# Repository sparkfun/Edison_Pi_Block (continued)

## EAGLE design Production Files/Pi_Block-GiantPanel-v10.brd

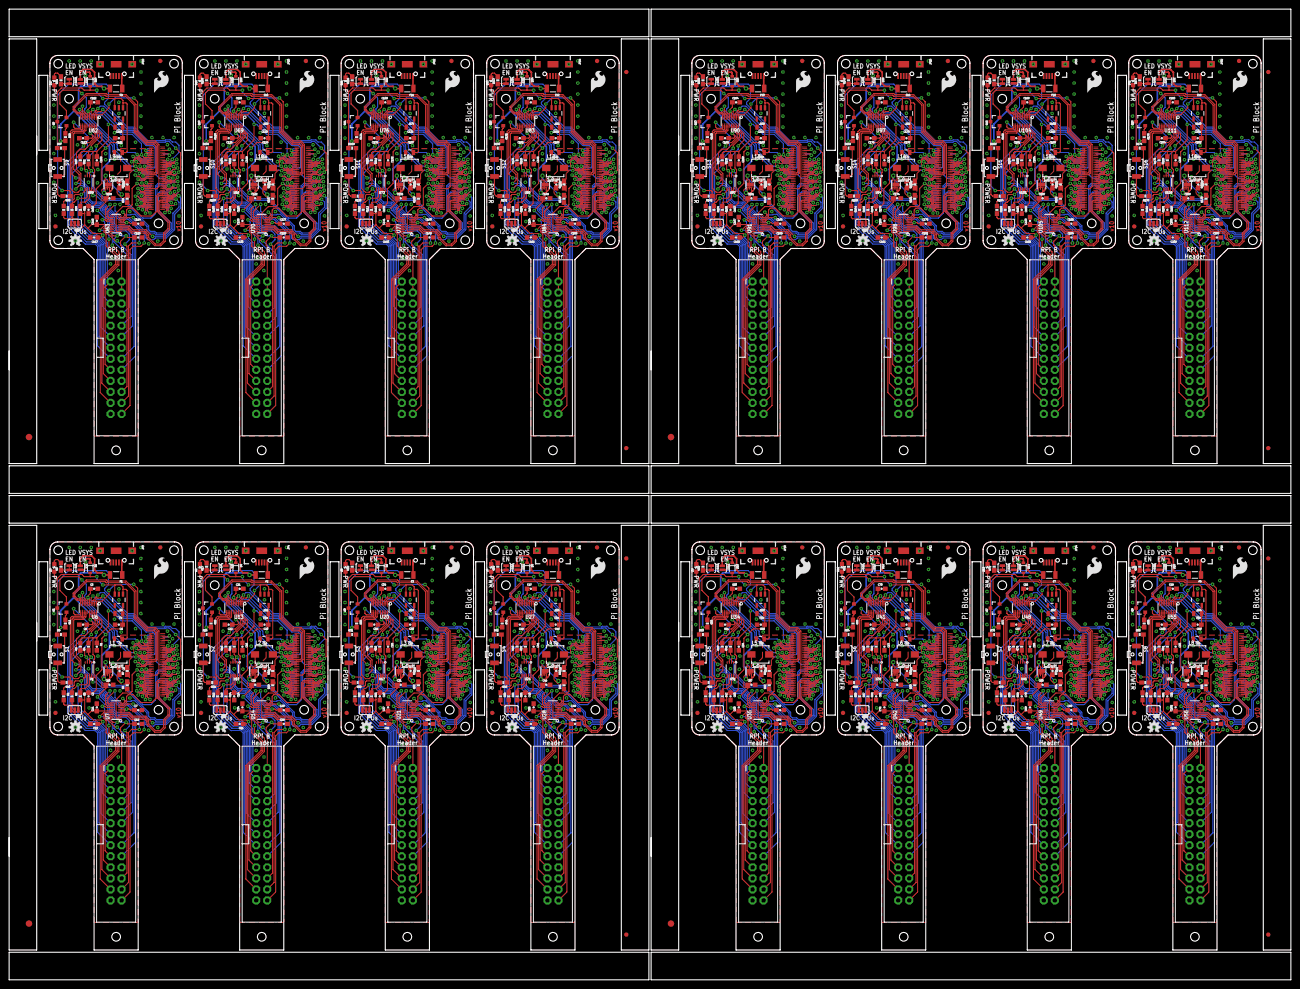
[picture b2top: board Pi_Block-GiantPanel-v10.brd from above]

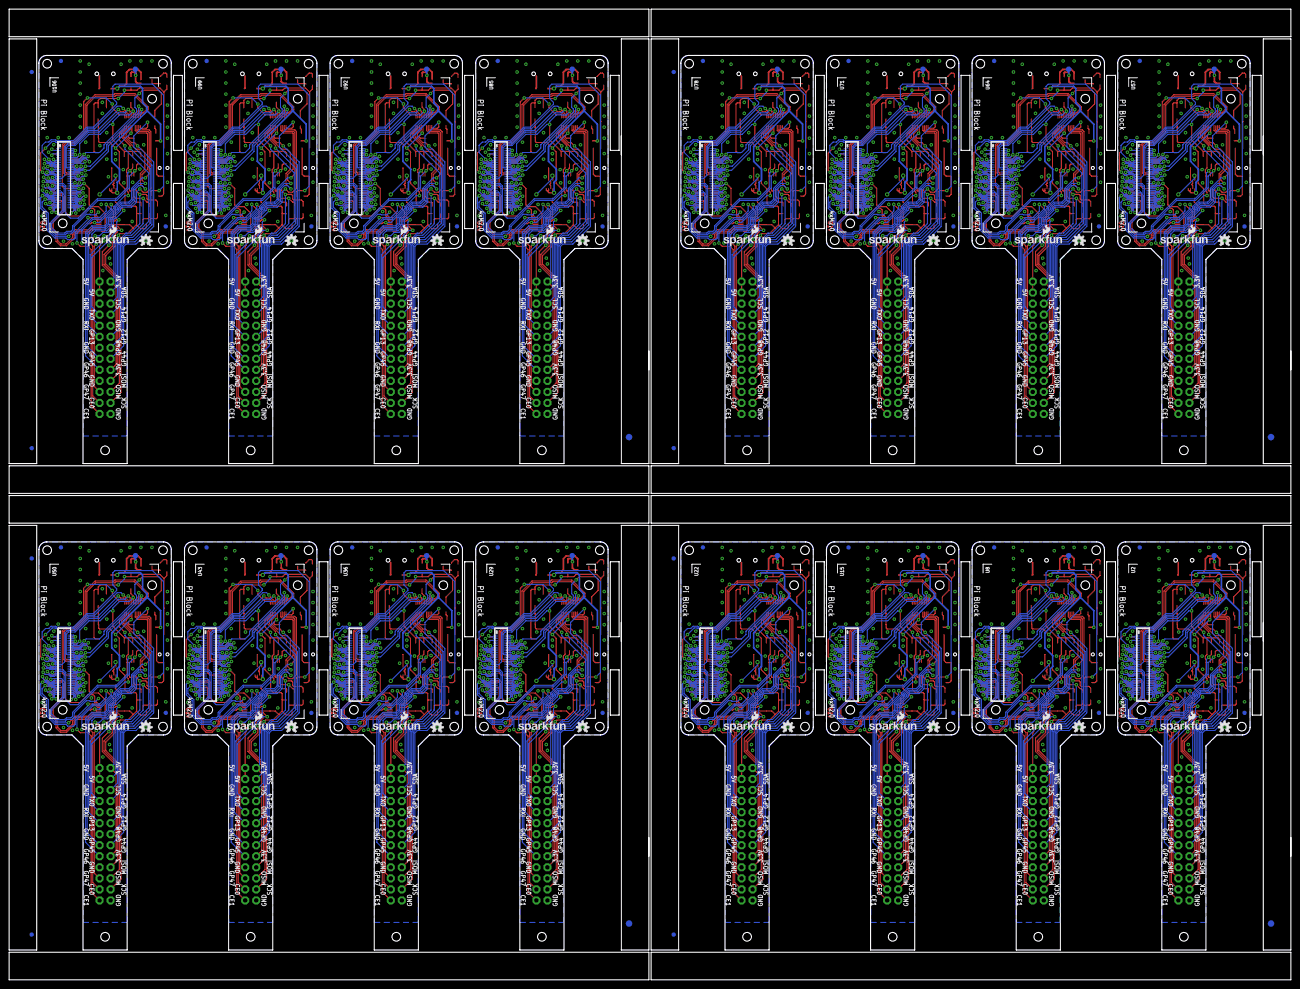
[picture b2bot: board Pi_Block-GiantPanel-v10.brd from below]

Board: 2 copper layers, 295.1 x 223.5 mm, 840 parts (124 on the bottom side), 1408 nets.

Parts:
C1, C2, C4, C5, C6, C7, C11, C14, C15, C20, C21, C22, C23, C24, C27, C28, C33, C34, C35, C36, C37, C40, C41, C46, C47, C48, C49, C50, C53, C54, C59, C60, C61, C62, C63, C66, C67, C72, C73, C74, C75, C76, C79, C80, C85, C86, C87, C88, C89, C92, C93, C98, C99, C100, C101, C102, C105, C106, C111, C112, C113, C114, C115, C118, C119, C124, C125, C126, C127, C128, C131, C132, C137, C138, C139, C140, C141, C144, C145, C150, C151, C152, C153, C154, C157, C158, C163, C164, C165, C166, C167, C170, C171, C176, C177, C178, C179, C180, C183, C184, C189, C190, C191, C192, C193, C196, C197, C202, C203, C204, C205, C206: 0.1uF; 0603-CAP
C3, C19, C32, C45, C58, C71, C84, C97, C110, C123, C136, C149, C162, C175, C188, C201: 10uF; 0805
C8, C16, C29, C42, C55, C68, C81, C94, C107, C120, C133, C146, C159, C172, C185, C198: 22uF; 0805
C9, C17, C30, C43, C56, C69, C82, C95, C108, C121, C134, C147, C160, C173, C186, C199: 9.0pF; 0603-CAP
C10, C18, C31, C44, C57, C70, C83, C96, C109, C122, C135, C148, C161, C174, C187, C200: 4.7uF; 0603-CAP
C12, C13, C25, C26, C38, C39, C51, C52, C64, C65, C77, C78, C90, C91, C103, C104, C116, C117, C129, C130, C142, C143, C155, C156, C168, C169, C181, C182, C194, C195, C207, C208: 1.0uF; 0603-CAP
D1, D4, D6, D8, D10, D12, D14, D16, D18, D20, D22, D24, D26, D28, D30, D32: BAT20J; SOD-323
D2, D3, D5, D7, D9, D11, D13, D15, D17, D19, D21, D23, D25, D27, D29, D31: BLUE; LED-0603
E$1, E$2, E$9, E$10, E$15, E$16, E$21, E$22: FIDUCIAL-1.5X3
E$3, E$4, E$5, E$6, E$7, E$8, E$11, E$12, E$13, E$14, E$17, E$18, E$19, E$20, E$23, E$24: FIDUCIAL-1X2
F1, F2, F3, F4, F5, F6, F7, F8, F9, F10, F11, F12, F13, F14, F15, F16: PTCSMD; PTC-1206
FID1, FID2, FID3, FID4, FID5, FID6, FID7, FID8, FID9, FID10, FID11, FID12, FID13, FID14, FID15, FID16, FID17, FID18, FID19, FID20, FID21, FID22, FID23, FID24, FID25, FID26, FID27, FID28, FID29, FID30, FID31, FID32, FID33, FID34, FID35, FID36, FID37, FID38, FID39, FID40, FID41, FID42, FID43, FID44, FID45, FID46, FID47, FID48, FID49, FID50, FID51, FID52, FID53, FID54, FID55, FID56, FID57, FID58, FID59, FID60, FID61, FID62, FID63, FID64: FIDUCIAL1X2; FIDUCIAL-1X2
JP1, JP2, JP5, JP7, JP9, JP11, JP13, JP15, JP17, JP19, JP21, JP23, JP25, JP27, JP29, JP31: RASPBERRYPI-GPIOPTH; 2X13-SHROUDED
JP3, JP4, JP6, JP8, JP10, JP12, JP14, JP16, JP18, JP20, JP22, JP24, JP26, JP28, JP30, JP32: USB_MICROB; USB-B-MICRO-SMD_V03
L1, L2, L3, L4, L5, L6, L7, L8, L9, L10, L11, L12, L13, L14, L15, L16: 1.0uH; INDUCTOR-SRP4020
LOGO1, LOGO2, LOGO5, LOGO6, LOGO9, LOGO10, LOGO13, LOGO14, LOGO17, LOGO18, LOGO21, LOGO22, LOGO25, LOGO26, LOGO29, LOGO30, LOGO33, LOGO34, LOGO37, LOGO38, LOGO41, LOGO42, LOGO45, LOGO46, LOGO49, LOGO50, LOGO53, LOGO54, LOGO57, LOGO58, LOGO61, LOGO62: OSHW-LOGOS; OSHW-LOGO-S
LOGO3, LOGO8, LOGO12, LOGO16, LOGO20, LOGO24, LOGO28, LOGO32, LOGO36, LOGO40, LOGO44, LOGO48, LOGO52, LOGO56, LOGO60, LOGO64: SFE_LOGO_FLAME.2_INCH; SFE_LOGO_FLAME_.2
LOGO4, LOGO7, LOGO11, LOGO15, LOGO19, LOGO23, LOGO27, LOGO31, LOGO35, LOGO39, LOGO43, LOGO47, LOGO51, LOGO55, LOGO59, LOGO63: SFE_LOGO_NAME_FLAME.1_INCH; SFE_LOGO_NAME_FLAME_.1
Q1, Q2, Q3, Q4, Q5, Q6, Q7, Q8, Q9, Q10, Q11, Q12, Q13, Q14, Q15, Q16: 200mA/50V; SOT23-3
R1, R2, R9, R12, R13, R20, R23, R24, R31, R34, R35, R42, R45, R46, R53, R56, R57, R64, R67, R68, R75, R78, R79, R86, R89, R90, R97, R100, R101, R108, R111, R112, R119, R122, R123, R130, R133, R134, R141, R144, R145, R152, R155, R156, R163, R166, R167, R174: 10K; 0603-RES
R3, R14, R25, R36, R47, R58, R69, R80, R91, R102, R113, R124, R135, R146, R157, R168: 200k; 0603-RES
R4, R5, R15, R16, R26, R27, R37, R38, R48, R49, R59, R60, R70, R71, R81, R82, R92, R93, R103, R104, R114, R115, R125, R126, R136, R137, R147, R148, R158, R159, R169, R170: DNP; 0603-RES
R6, R11, R17, R22, R28, R33, R39, R44, R50, R55, R61, R66, R72, R77, R83, R88, R94, R99, R105, R110, R116, R121, R127, R132, R138, R143, R149, R154, R160, R165, R171, R176: 1K; 0603-RES
R7, R18, R29, R40, R51, R62, R73, R84, R95, R106, R117, R128, R139, R150, R161, R172: 680k; 0603-RES
R8, R19, R30, R41, R52, R63, R74, R85, R96, R107, R118, R129, R140, R151, R162, R173: 120k; 0603-RES
R10, R21, R32, R43, R54, R65, R76, R87, R98, R109, R120, R131, R142, R153, R164, R175: 220; 0603-RES
S1, S2, S3, S4, S5, S6, S7, S8, S9, S10, S11, S12, S13, S14, S15, S16: POWER; TACTILE_SWITCH-SMD-RIGHT-ANGLE
SJ1, SJ5, SJ8, SJ11, SJ14, SJ17, SJ20, SJ23, SJ26, SJ29, SJ32, SJ35, SJ38, SJ41, SJ44, SJ47: JUMPER-PAD-2-NOYES_SILK; PAD-JUMPER-2-NO_YES_SILK
SJ2, SJ6, SJ9, SJ12, SJ15, SJ18, SJ21, SJ24, SJ27, SJ30, SJ33, SJ36, SJ39, SJ42, SJ45, SJ48: JUMPER-PAD-3-NC_BY_PASTE; PAD-JUMPER-3-NC_BY_PASTE_YES_SILK_FULL_BOX
SJ3, SJ4, SJ7, SJ10, SJ13, SJ16, SJ19, SJ22, SJ25, SJ28, SJ31, SJ34, SJ37, SJ40, SJ43, SJ46: JUMPER-PAD-2-NC_BY_TRACE; PAD-JUMPER-2-NC_BY_TRACE_YES_SILK
TP1, TP2, TP3, TP4, TP5, TP6, TP7, TP8, TP9, TP10, TP11, TP12, TP13, TP14, TP15, TP16: TEST-POINT3X5; PAD.03X.05
U1, U10, U17, U24, U31, U38, U45, U52, U59, U66, U73, U80, U87, U94, U101, U108: PCA9306; PCA9306DC-1:1
U2, U8, U15, U22, U29, U36, U43, U50, U57, U64, U71, U78, U85, U92, U99, U106: EDISON_CONNECTOR_FULLMOUNTING_HOLES; EDISON_DAUGHTER
U3, U9, U16, U23, U30, U37, U44, U51, U58, U65, U72, U79, U86, U93, U100, U107: EDISON_CONNECTOR_FULLHEADER; DF40C-70DP-0.4(51)
U4, U11, U18, U25, U32, U39, U46, U53, U60, U67, U74, U81, U88, U95, U102, U109: TPS62065; WSON-8-PAD
U5, U12, U19, U26, U33, U40, U47, U54, U61, U68, U75, U82, U89, U96, U103, U110: MIC5219 3.3V; SOT23-5
U6, U7, U13, U14, U20, U21, U27, U28, U34, U35, U41, U42, U48, U49, U55, U56, U62, U63, U69, U70, U76, U77, U83, U84, U90, U91, U97, U98, U104, U105, U111, U112: TXB0108; UFDFN-20

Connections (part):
1.8V: C1.1, C5.1, C7.1, R4.2, R5.2, U1.1, U2.12, U3.12, U6.5, U6.6, U7.5, U7.6
1.8V1: C15.1, C21.1, C23.1, R15.2, R16.2, U8.12, U9.12, U10.1, U13.5, U13.6, U14.5, U14.6
1.8V2: C28.1, C34.1, C36.1, R26.2, R27.2, U15.12, U16.12, U17.1, U20.5, U20.6, U21.5, U21.6
1.8V3: C41.1, C47.1, C49.1, R37.2, R38.2, U22.12, U23.12, U24.1, U27.5, U27.6, U28.5, U28.6
1.8V4: C54.1, C60.1, C62.1, R48.2, R49.2, U29.12, U30.12, U31.1, U34.5, U34.6, U35.5, U35.6
1.8V5: C67.1, C73.1, C75.1, R59.2, R60.2, U36.12, U37.12, U38.1, U41.5, U41.6, U42.5, U42.6
1.8V6: C80.1, C86.1, C88.1, R70.2, R71.2, U43.12, U44.12, U45.1, U48.5, U48.6, U49.5, U49.6
1.8V7: C93.1, C99.1, C101.1, R81.2, R82.2, U50.12, U51.12, U52.1, U55.5, U55.6, U56.5, U56.6
1.8V8: C106.1, C112.1, C114.1, R92.2, R93.2, U57.12, U58.12, U59.1, U62.5, U62.6, U63.5, U63.6
1.8V9: C119.1, C125.1, C127.1, R103.2, R104.2, U64.12, U65.12, U66.1, U69.5, U69.6, U70.5, U70.6
1.8V10: C132.1, C138.1, C140.1, R114.2, R115.2, U71.12, U72.12, U73.1, U76.5, U76.6, U77.5, U77.6
1.8V11: C145.1, C151.1, C153.1, R125.2, R126.2, U78.12, U79.12, U80.1, U83.5, U83.6, U84.5, U84.6
1.8V12: C158.1, C164.1, C166.1, R136.2, R137.2, U85.12, U86.12, U87.1, U90.5, U90.6, U91.5, U91.6
1.8V13: C171.1, C177.1, C179.1, R147.2, R148.2, U92.12, U93.12, U94.1, U97.5, U97.6, U98.5, U98.6
1.8V14: C184.1, C190.1, C192.1, R158.2, R159.2, U99.12, U100.12, U101.1, U104.5, U104.6, U105.5, U105.6
1.8V15: C197.1, C203.1, C205.1, R169.2, R170.2, U106.12, U107.12, U108.1, U111.5, U111.6, U112.5, U112.6
3.3V: U2.8, U2.10, U3.8, U3.10
3.3V1: U8.8, U8.10, U9.8, U9.10
3.3V2: U15.8, U15.10, U16.8, U16.10
3.3V3: U22.8, U22.10, U23.8, U23.10
3.3V4: U29.8, U29.10, U30.8, U30.10
3.3V5: U36.8, U36.10, U37.8, U37.10
3.3V6: U43.8, U43.10, U44.8, U44.10
3.3V7: U50.8, U50.10, U51.8, U51.10
3.3V8: U57.8, U57.10, U58.8, U58.10
3.3V9: U64.8, U64.10, U65.8, U65.10
3.3V10: U71.8, U71.10, U72.8, U72.10
3.3V11: U78.8, U78.10, U79.8, U79.10
3.3V12: U85.8, U85.10, U86.8, U86.10
3.3V13: U92.8, U92.10, U93.8, U93.10
3.3V14: U99.8, U99.10, U100.8, U100.10
3.3V15: U106.8, U106.10, U107.8, U107.10
3.3V_LOCAL: C2.1, C3.1, C4.1, C6.1, C11.1, C13.1, JP1.1, JP1.17, R3.2, SJ2.2, U5.5, U6.16, U7.16
3.3V_LOCAL1: C14.1, C19.1, C20.1, C22.1, C24.1, C26.1, JP2.1, JP2.17, R14.2, SJ6.2, U12.5, U13.16, U14.16
3.3V_LOCAL2: C27.1, C32.1, C33.1, C35.1, C37.1, C39.1, JP5.1, JP5.17, R25.2, SJ9.2, U19.5, U20.16, U21.16
3.3V_LOCAL3: C40.1, C45.1, C46.1, C48.1, C50.1, C52.1, JP7.1, JP7.17, R36.2, SJ12.2, U26.5, U27.16, U28.16
3.3V_LOCAL4: C53.1, C58.1, C59.1, C61.1, C63.1, C65.1, JP9.1, JP9.17, R47.2, SJ15.2, U33.5, U34.16, U35.16
3.3V_LOCAL5: C66.1, C71.1, C72.1, C74.1, C76.1, C78.1, JP11.1, JP11.17, R58.2, SJ18.2, U40.5, U41.16, U42.16
3.3V_LOCAL6: C79.1, C84.1, C85.1, C87.1, C89.1, C91.1, JP13.1, JP13.17, R69.2, SJ21.2, U47.5, U48.16, U49.16
3.3V_LOCAL7: C92.1, C97.1, C98.1, C100.1, C102.1, C104.1, JP15.1, JP15.17, R80.2, SJ24.2, U54.5, U55.16, U56.16
3.3V_LOCAL8: C105.1, C110.1, C111.1, C113.1, C115.1, C117.1, JP17.1, JP17.17, R91.2, SJ27.2, U61.5, U62.16, U63.16
3.3V_LOCAL9: C118.1, C123.1, C124.1, C126.1, C128.1, C130.1, JP19.1, JP19.17, R102.2, SJ30.2, U68.5, U69.16, U70.16
3.3V_LOCAL10: C131.1, C136.1, C137.1, C139.1, C141.1, C143.1, JP21.1, JP21.17, R113.2, SJ33.2, U75.5, U76.16, U77.16
3.3V_LOCAL11: C144.1, C149.1, C150.1, C152.1, C154.1, C156.1, JP23.1, JP23.17, R124.2, SJ36.2, U82.5, U83.16, U84.16
3.3V_LOCAL12: C157.1, C162.1, C163.1, C165.1, C167.1, C169.1, JP25.1, JP25.17, R135.2, SJ39.2, U89.5, U90.16, U91.16
3.3V_LOCAL13: C170.1, C175.1, C176.1, C178.1, C180.1, C182.1, JP27.1, JP27.17, R146.2, SJ42.2, U96.5, U97.16, U98.16
3.3V_LOCAL14: C183.1, C188.1, C189.1, C191.1, C193.1, C195.1, JP29.1, JP29.17, R157.2, SJ45.2, U103.5, U104.16, U105.16
3.3V_LOCAL15: C196.1, C201.1, C202.1, C204.1, C206.1, C208.1, JP31.1, JP31.17, R168.2, SJ48.2, U110.5, U111.16, U112.16
5V: C10.1, C12.1, F1.2, JP1.2, JP1.4, R11.2, SJ1.1, U4.5, U4.7, U4.8
5V1: C18.1, C25.1, F2.2, JP2.2, JP2.4, R22.2, SJ5.1, U11.5, U11.7, U11.8
5V2: C31.1, C38.1, F3.2, JP5.2, JP5.4, R33.2, SJ8.1, U18.5, U18.7, U18.8
5V3: C44.1, C51.1, F4.2, JP7.2, JP7.4, R44.2, SJ11.1, U25.5, U25.7, U25.8
5V4: C57.1, C64.1, F5.2, JP9.2, JP9.4, R55.2, SJ14.1, U32.5, U32.7, U32.8
5V5: C70.1, C77.1, F6.2, JP11.2, JP11.4, R66.2, SJ17.1, U39.5, U39.7, U39.8
5V6: C83.1, C90.1, F7.2, JP13.2, JP13.4, R77.2, SJ20.1, U46.5, U46.7, U46.8
5V7: C96.1, C103.1, F8.2, JP15.2, JP15.4, R88.2, SJ23.1, U53.5, U53.7, U53.8
5V8: C109.1, C116.1, F9.2, JP17.2, JP17.4, R99.2, SJ26.1, U60.5, U60.7, U60.8
5V9: C122.1, C129.1, F10.2, JP19.2, JP19.4, R110.2, SJ29.1, U67.5, U67.7, U67.8
5V10: C135.1, C142.1, F11.2, JP21.2, JP21.4, R121.2, SJ32.1, U74.5, U74.7, U74.8
5V11: C148.1, C155.1, F12.2, JP23.2, JP23.4, R132.2, SJ35.1, U81.5, U81.7, U81.8
5V12: C161.1, C168.1, F13.2, JP25.2, JP25.4, R143.2, SJ38.1, U88.5, U88.7, U88.8
5V13: C174.1, C181.1, F14.2, JP27.2, JP27.4, R154.2, SJ41.1, U95.5, U95.7, U95.8
5V14: C187.1, C194.1, F15.2, JP29.2, JP29.4, R165.2, SJ44.1, U102.5, U102.7, U102.8
5V15: C200.1, C207.1, F16.2, JP31.2, JP31.4, R176.2, SJ47.1, U109.5, U109.7, U109.8
DCIN: Q1.2, U2.14, U3.14
DCIN1: Q2.2, U8.14, U9.14
DCIN2: Q3.2, U15.14, U16.14
DCIN3: Q4.2, U22.14, U23.14
DCIN4: Q5.2, U29.14, U30.14
DCIN5: Q6.2, U36.14, U37.14
DCIN6: Q7.2, U43.14, U44.14
DCIN7: Q8.2, U50.14, U51.14
DCIN8: Q9.2, U57.14, U58.14
DCIN9: Q10.2, U64.14, U65.14
DCIN10: Q11.2, U71.14, U72.14
DCIN11: Q12.2, U78.14, U79.14
DCIN12: Q13.2, U85.14, U86.14
DCIN13: Q14.2, U92.14, U93.14
DCIN14: Q15.2, U99.14, U100.14
DCIN15: Q16.2, U106.14, U107.14
FAULT: U2.19, U3.19
FAULT1: U8.19, U9.19
FAULT2: U15.19, U16.19
FAULT3: U22.19, U23.19
FAULT4: U29.19, U30.19
FAULT5: U36.19, U37.19
FAULT6: U43.19, U44.19
FAULT7: U50.19, U51.19
FAULT8: U57.19, U58.19
FAULT9: U64.19, U65.19
FAULT10: U71.19, U72.19
FAULT11: U78.19, U79.19
FAULT12: U85.19, U86.19
FAULT13: U92.19, U93.19
FAULT14: U99.19, U100.19
FAULT15: U106.19, U107.19
FW_RCVR: U2.69, U3.69
FW_RCVR1: U8.69, U9.69
FW_RCVR2: U15.69, U16.69
FW_RCVR3: U22.69, U23.69
FW_RCVR4: U29.69, U30.69
FW_RCVR5: U36.69, U37.69
FW_RCVR6: U43.69, U44.69
FW_RCVR7: U50.69, U51.69
FW_RCVR8: U57.69, U58.69
FW_RCVR9: U64.69, U65.69
FW_RCVR10: U71.69, U72.69
FW_RCVR11: U78.69, U79.69
FW_RCVR12: U85.69, U86.69
FW_RCVR13: U92.69, U93.69
FW_RCVR14: U99.69, U100.69
FW_RCVR15: U106.69, U107.69
GND: C1.2, C2.2, C3.2, C4.2, C5.2, C6.2, C7.2, C8.2, C10.2, C11.2, C12.2, C13.2, JP1.6, JP1.9, JP1.14, JP1.20, JP1.25, JP3.GND1, JP3.SHIELD1, JP3.SHIELD2, JP3.SHIELD3, R8.1, S1.1, SJ3.1, U1.4, U2.1, U2.5, U2.9, U2.11, U2.13, U2.15, U3.1, U3.5, U3.9, U3.11, U3.13, U3.15, U4.1, U4.3, U4.6, U4.PAD, U5.2, U6.15, U7.15
GND1: C14.2, C15.2, C16.2, C18.2, C19.2, C20.2, C21.2, C22.2, C23.2, C24.2, C25.2, C26.2, JP2.6, JP2.9, JP2.14, JP2.20, JP2.25, JP4.GND1, JP4.SHIELD1, JP4.SHIELD2, JP4.SHIELD3, R19.1, S2.1, SJ4.1, U8.1, U8.5, U8.9, U8.11, U8.13, U8.15, U9.1, U9.5, U9.9, U9.11, U9.13, U9.15, U10.4, U11.1, U11.3, U11.6, U11.PAD, U12.2, U13.15, U14.15
GND2: C27.2, C28.2, C29.2, C31.2, C32.2, C33.2, C34.2, C35.2, C36.2, C37.2, C38.2, C39.2, JP5.6, JP5.9, JP5.14, JP5.20, JP5.25, JP6.GND1, JP6.SHIELD1, JP6.SHIELD2, JP6.SHIELD3, R30.1, S3.1, SJ7.1, U15.1, U15.5, U15.9, U15.11, U15.13, U15.15, U16.1, U16.5, U16.9, U16.11, U16.13, U16.15, U17.4, U18.1, U18.3, U18.6, U18.PAD, U19.2, U20.15, U21.15
GND3: C40.2, C41.2, C42.2, C44.2, C45.2, C46.2, C47.2, C48.2, C49.2, C50.2, C51.2, C52.2, JP7.6, JP7.9, JP7.14, JP7.20, JP7.25, JP8.GND1, JP8.SHIELD1, JP8.SHIELD2, JP8.SHIELD3, R41.1, S4.1, SJ10.1, U22.1, U22.5, U22.9, U22.11, U22.13, U22.15, U23.1, U23.5, U23.9, U23.11, U23.13, U23.15, U24.4, U25.1, U25.3, U25.6, U25.PAD, U26.2, U27.15, U28.15
GND4: C53.2, C54.2, C55.2, C57.2, C58.2, C59.2, C60.2, C61.2, C62.2, C63.2, C64.2, C65.2, JP9.6, JP9.9, JP9.14, JP9.20, JP9.25, JP10.GND1, JP10.SHIELD1, JP10.SHIELD2, JP10.SHIELD3, R52.1, S5.1, SJ13.1, U29.1, U29.5, U29.9, U29.11, U29.13, U29.15, U30.1, U30.5, U30.9, U30.11, U30.13, U30.15, U31.4, U32.1, U32.3, U32.6, U32.PAD, U33.2, U34.15, U35.15
GND5: C66.2, C67.2, C68.2, C70.2, C71.2, C72.2, C73.2, C74.2, C75.2, C76.2, C77.2, C78.2, JP11.6, JP11.9, JP11.14, JP11.20, JP11.25, JP12.GND1, JP12.SHIELD1, JP12.SHIELD2, JP12.SHIELD3, R63.1, S6.1, SJ16.1, U36.1, U36.5, U36.9, U36.11, U36.13, U36.15, U37.1, U37.5, U37.9, U37.11, U37.13, U37.15, U38.4, U39.1, U39.3, U39.6, U39.PAD, U40.2, U41.15, U42.15
GND6: C79.2, C80.2, C81.2, C83.2, C84.2, C85.2, C86.2, C87.2, C88.2, C89.2, C90.2, C91.2, JP13.6, JP13.9, JP13.14, JP13.20, JP13.25, JP14.GND1, JP14.SHIELD1, JP14.SHIELD2, JP14.SHIELD3, R74.1, S7.1, SJ19.1, U43.1, U43.5, U43.9, U43.11, U43.13, U43.15, U44.1, U44.5, U44.9, U44.11, U44.13, U44.15, U45.4, U46.1, U46.3, U46.6, U46.PAD, U47.2, U48.15, U49.15
GND7: C92.2, C93.2, C94.2, C96.2, C97.2, C98.2, C99.2, C100.2, C101.2, C102.2, C103.2, C104.2, JP15.6, JP15.9, JP15.14, JP15.20, JP15.25, JP16.GND1, JP16.SHIELD1, JP16.SHIELD2, JP16.SHIELD3, R85.1, S8.1, SJ22.1, U50.1, U50.5, U50.9, U50.11, U50.13, U50.15, U51.1, U51.5, U51.9, U51.11, U51.13, U51.15, U52.4, U53.1, U53.3, U53.6, U53.PAD, U54.2, U55.15, U56.15
GND8: C105.2, C106.2, C107.2, C109.2, C110.2, C111.2, C112.2, C113.2, C114.2, C115.2, C116.2, C117.2, JP17.6, JP17.9, JP17.14, JP17.20, JP17.25, JP18.GND1, JP18.SHIELD1, JP18.SHIELD2, JP18.SHIELD3, R96.1, S9.1, SJ25.1, U57.1, U57.5, U57.9, U57.11, U57.13, U57.15, U58.1, U58.5, U58.9, U58.11, U58.13, U58.15, U59.4, U60.1, U60.3, U60.6, U60.PAD, U61.2, U62.15, U63.15
GND9: C118.2, C119.2, C120.2, C122.2, C123.2, C124.2, C125.2, C126.2, C127.2, C128.2, C129.2, C130.2, JP19.6, JP19.9, JP19.14, JP19.20, JP19.25, JP20.GND1, JP20.SHIELD1, JP20.SHIELD2, JP20.SHIELD3, R107.1, S10.1, SJ28.1, U64.1, U64.5, U64.9, U64.11, U64.13, U64.15, U65.1, U65.5, U65.9, U65.11, U65.13, U65.15, U66.4, U67.1, U67.3, U67.6, U67.PAD, U68.2, U69.15, U70.15
GND10: C131.2, C132.2, C133.2, C135.2, C136.2, C137.2, C138.2, C139.2, C140.2, C141.2, C142.2, C143.2, JP21.6, JP21.9, JP21.14, JP21.20, JP21.25, JP22.GND1, JP22.SHIELD1, JP22.SHIELD2, JP22.SHIELD3, R118.1, S11.1, SJ31.1, U71.1, U71.5, U71.9, U71.11, U71.13, U71.15, U72.1, U72.5, U72.9, U72.11, U72.13, U72.15, U73.4, U74.1, U74.3, U74.6, U74.PAD, U75.2, U76.15, U77.15
GND11: C144.2, C145.2, C146.2, C148.2, C149.2, C150.2, C151.2, C152.2, C153.2, C154.2, C155.2, C156.2, JP23.6, JP23.9, JP23.14, JP23.20, JP23.25, JP24.GND1, JP24.SHIELD1, JP24.SHIELD2, JP24.SHIELD3, R129.1, S12.1, SJ34.1, U78.1, U78.5, U78.9, U78.11, U78.13, U78.15, U79.1, U79.5, U79.9, U79.11, U79.13, U79.15, U80.4, U81.1, U81.3, U81.6, U81.PAD, U82.2, U83.15, U84.15
GND12: C157.2, C158.2, C159.2, C161.2, C162.2, C163.2, C164.2, C165.2, C166.2, C167.2, C168.2, C169.2, JP25.6, JP25.9, JP25.14, JP25.20, JP25.25, JP26.GND1, JP26.SHIELD1, JP26.SHIELD2, JP26.SHIELD3, R140.1, S13.1, SJ37.1, U85.1, U85.5, U85.9, U85.11, U85.13, U85.15, U86.1, U86.5, U86.9, U86.11, U86.13, U86.15, U87.4, U88.1, U88.3, U88.6, U88.PAD, U89.2, U90.15, U91.15
GND13: C170.2, C171.2, C172.2, C174.2, C175.2, C176.2, C177.2, C178.2, C179.2, C180.2, C181.2, C182.2, JP27.6, JP27.9, JP27.14, JP27.20, JP27.25, JP28.GND1, JP28.SHIELD1, JP28.SHIELD2, JP28.SHIELD3, R151.1, S14.1, SJ40.1, U92.1, U92.5, U92.9, U92.11, U92.13, U92.15, U93.1, U93.5, U93.9, U93.11, U93.13, U93.15, U94.4, U95.1, U95.3, U95.6, U95.PAD, U96.2, U97.15, U98.15
GND14: C183.2, C184.2, C185.2, C187.2, C188.2, C189.2, C190.2, C191.2, C192.2, C193.2, C194.2, C195.2, JP29.6, JP29.9, JP29.14, JP29.20, JP29.25, JP30.GND1, JP30.SHIELD1, JP30.SHIELD2, JP30.SHIELD3, R162.1, S15.1, SJ43.1, U99.1, U99.5, U99.9, U99.11, U99.13, U99.15, U100.1, U100.5, U100.9, U100.11, U100.13, U100.15, U101.4, U102.1, U102.3, U102.6, U102.PAD, U103.2, U104.15, U105.15
GND15: C196.2, C197.2, C198.2, C200.2, C201.2, C202.2, C203.2, C204.2, C205.2, C206.2, C207.2, C208.2, JP31.6, JP31.9, JP31.14, JP31.20, JP31.25, JP32.GND1, JP32.SHIELD1, JP32.SHIELD2, JP32.SHIELD3, R173.1, S16.1, SJ46.1, U106.1, U106.5, U106.9, U106.11, U106.13, U106.15, U107.1, U107.5, U107.9, U107.11, U107.13, U107.15, U108.4, U109.1, U109.3, U109.6, U109.PAD, U110.2, U111.15, U112.15
GP1: U8.48, U9.48, U13.1
GP2: U8.42, U9.42
GP3: U8.34, U9.34
GP4: U8.32, U9.32, U13.10
GP5: U8.30, U9.30, U13.9
GP6: U8.28, U9.28, U13.8
GP7: U8.26, U9.26, U13.7
GP8: U8.25, U9.25
GP9: U8.24, U9.24, U13.4
GP10: U15.48, U16.48, U20.1
GP11: U15.42, U16.42
GP12: U15.34, U16.34
GP12_PWM0: U2.35, U3.35, U6.2
GP12_PWM1: U8.35, U9.35, U13.2
GP12_PWM2: U15.35, U16.35, U20.2
GP12_PWM3: U22.35, U23.35, U27.2
GP12_PWM4: U29.35, U30.35, U34.2
GP12_PWM5: U36.35, U37.35, U41.2
GP12_PWM6: U43.35, U44.35, U48.2
GP12_PWM7: U50.35, U51.35, U55.2
GP12_PWM8: U57.35, U58.35, U62.2
GP12_PWM9: U64.35, U65.35, U69.2
GP12_PWM10: U71.35, U72.35, U76.2
GP12_PWM11: U78.35, U79.35, U83.2
GP12_PWM12: U85.35, U86.35, U90.2
GP12_PWM13: U92.35, U93.35, U97.2
GP12_PWM14: U99.35, U100.35, U104.2
GP12_PWM15: U106.35, U107.35, U111.2
GP13: U15.32, U16.32, U20.10
GP13_PWM1: U2.33, U3.33, U6.3
GP13_PWM2: U8.33, U9.33, U13.3
GP13_PWM3: U15.33, U16.33, U20.3
GP13_PWM4: U22.33, U23.33, U27.3
GP13_PWM5: U29.33, U30.33, U34.3
GP13_PWM6: U36.33, U37.33, U41.3
GP13_PWM7: U43.33, U44.33, U48.3
GP13_PWM8: U50.33, U51.33, U55.3
GP13_PWM9: U57.33, U58.33, U62.3
GP13_PWM10: U64.33, U65.33, U69.3
GP13_PWM11: U71.33, U72.33, U76.3
GP13_PWM12: U78.33, U79.33, U83.3
GP13_PWM13: U85.33, U86.33, U90.3
GP13_PWM14: U92.33, U93.33, U97.3
GP13_PWM15: U99.33, U100.33, U104.3
GP13_PWM16: U106.33, U107.33, U111.3
GP14: U2.48, U3.48, U6.1
GP15: U2.42, U3.42
GP16: U15.30, U16.30, U20.9
GP17: U15.28, U16.28, U20.8
GP18: U15.26, U16.26, U20.7
GP19: U15.25, U16.25
GP19_I2C_1_SCL: R4.1, U1.2, U2.41, U3.41
GP19_I2C_1_SCL1: R15.1, U8.41, U9.41, U10.2
GP19_I2C_1_SCL2: R26.1, U15.41, U16.41, U17.2
GP19_I2C_1_SCL3: R37.1, U22.41, U23.41, U24.2
GP19_I2C_1_SCL4: R48.1, U29.41, U30.41, U31.2
GP19_I2C_1_SCL5: R59.1, U36.41, U37.41, U38.2
GP19_I2C_1_SCL6: R70.1, U43.41, U44.41, U45.2
GP19_I2C_1_SCL7: R81.1, U50.41, U51.41, U52.2
GP19_I2C_1_SCL8: R92.1, U57.41, U58.41, U59.2
GP19_I2C_1_SCL9: R103.1, U64.41, U65.41, U66.2
GP19_I2C_1_SCL10: R114.1, U71.41, U72.41, U73.2
GP19_I2C_1_SCL11: R125.1, U78.41, U79.41, U80.2
GP19_I2C_1_SCL12: R136.1, U85.41, U86.41, U87.2
GP19_I2C_1_SCL13: R147.1, U92.41, U93.41, U94.2
GP19_I2C_1_SCL14: R158.1, U99.41, U100.41, U101.2
GP19_I2C_1_SCL15: R169.1, U106.41, U107.41, U108.2
GP20: U15.24, U16.24, U20.4
GP20_I2C_1_SDA: R5.1, U1.3, U2.43, U3.43
GP20_I2C_1_SDA1: R16.1, U8.43, U9.43, U10.3
GP20_I2C_1_SDA2: R27.1, U15.43, U16.43, U17.3
GP20_I2C_1_SDA3: R38.1, U22.43, U23.43, U24.3
GP20_I2C_1_SDA4: R49.1, U29.43, U30.43, U31.3
GP20_I2C_1_SDA5: R60.1, U36.43, U37.43, U38.3
GP20_I2C_1_SDA6: R71.1, U43.43, U44.43, U45.3
GP20_I2C_1_SDA7: R82.1, U50.43, U51.43, U52.3
GP20_I2C_1_SDA8: R93.1, U57.43, U58.43, U59.3
GP20_I2C_1_SDA9: R104.1, U64.43, U65.43, U66.3
GP20_I2C_1_SDA10: R115.1, U71.43, U72.43, U73.3
GP20_I2C_1_SDA11: R126.1, U78.43, U79.43, U80.3
GP20_I2C_1_SDA12: R137.1, U85.43, U86.43, U87.3
GP20_I2C_1_SDA13: R148.1, U92.43, U93.43, U94.3
GP20_I2C_1_SDA14: R159.1, U99.43, U100.43, U101.3
GP20_I2C_1_SDA15: R170.1, U106.43, U107.43, U108.3
GP21: U22.48, U23.48, U27.1
GP22: U22.42, U23.42
GP23: U22.34, U23.34
GP24: U22.32, U23.32, U27.10
GP25: U22.30, U23.30, U27.9
GP26: U22.28, U23.28, U27.8
GP27: U22.26, U23.26, U27.7
GP27_I2C_6_SCL: U2.45, U3.45
GP27_I2C_6_SCL1: U8.45, U9.45
GP27_I2C_6_SCL2: U15.45, U16.45
GP27_I2C_6_SCL3: U22.45, U23.45
GP27_I2C_6_SCL4: U29.45, U30.45
GP27_I2C_6_SCL5: U36.45, U37.45
GP27_I2C_6_SCL6: U43.45, U44.45
GP27_I2C_6_SCL7: U50.45, U51.45
GP27_I2C_6_SCL8: U57.45, U58.45
GP27_I2C_6_SCL9: U64.45, U65.45
GP27_I2C_6_SCL10: U71.45, U72.45
GP27_I2C_6_SCL11: U78.45, U79.45
GP27_I2C_6_SCL12: U85.45, U86.45
GP27_I2C_6_SCL13: U92.45, U93.45
GP27_I2C_6_SCL14: U99.45, U100.45
GP27_I2C_6_SCL15: U106.45, U107.45
GP28: U22.25, U23.25
GP28_I2C_6_SDA: U2.47, U3.47
GP28_I2C_6_SDA1: U8.47, U9.47
GP28_I2C_6_SDA2: U15.47, U16.47
GP28_I2C_6_SDA3: U22.47, U23.47
GP28_I2C_6_SDA4: U29.47, U30.47
GP28_I2C_6_SDA5: U36.47, U37.47
GP28_I2C_6_SDA6: U43.47, U44.47
GP28_I2C_6_SDA7: U50.47, U51.47
GP28_I2C_6_SDA8: U57.47, U58.47
GP28_I2C_6_SDA9: U64.47, U65.47
GP28_I2C_6_SDA10: U71.47, U72.47
GP28_I2C_6_SDA11: U78.47, U79.47
GP28_I2C_6_SDA12: U85.47, U86.47
GP28_I2C_6_SDA13: U92.47, U93.47
GP28_I2C_6_SDA14: U99.47, U100.47
GP28_I2C_6_SDA15: U106.47, U107.47
GP29: U22.24, U23.24, U27.4
GP30: U29.48, U30.48, U34.1
GP31: U29.42, U30.42
GP32: U29.34, U30.34
GP33: U29.32, U30.32, U34.10
GP34: U29.30, U30.30, U34.9
GP35: U29.28, U30.28, U34.8
GP36: U29.26, U30.26, U34.7
GP37: U29.25, U30.25
GP38: U29.24, U30.24, U34.4
GP39: U36.48, U37.48, U41.1
GP40: U36.42, U37.42
GP40_I2S_2_CLK: U2.52, U3.52
GP40_I2S_2_CLK1: U8.52, U9.52
GP40_I2S_2_CLK2: U15.52, U16.52
GP40_I2S_2_CLK3: U22.52, U23.52
GP40_I2S_2_CLK4: U29.52, U30.52
GP40_I2S_2_CLK5: U36.52, U37.52
GP40_I2S_2_CLK6: U43.52, U44.52
GP40_I2S_2_CLK7: U50.52, U51.52
GP40_I2S_2_CLK8: U57.52, U58.52
GP40_I2S_2_CLK9: U64.52, U65.52
GP40_I2S_2_CLK10: U71.52, U72.52
GP40_I2S_2_CLK11: U78.52, U79.52
GP40_I2S_2_CLK12: U85.52, U86.52
GP40_I2S_2_CLK13: U92.52, U93.52
GP40_I2S_2_CLK14: U99.52, U100.52
GP40_I2S_2_CLK15: U106.52, U107.52
GP41: U36.34, U37.34
GP41_I2S_2_FS: U2.54, U3.54
GP41_I2S_2_FS1: U8.54, U9.54
GP41_I2S_2_FS2: U15.54, U16.54
GP41_I2S_2_FS3: U22.54, U23.54
GP41_I2S_2_FS4: U29.54, U30.54
GP41_I2S_2_FS5: U36.54, U37.54
GP41_I2S_2_FS6: U43.54, U44.54
GP41_I2S_2_FS7: U50.54, U51.54
GP41_I2S_2_FS8: U57.54, U58.54
GP41_I2S_2_FS9: U64.54, U65.54
GP41_I2S_2_FS10: U71.54, U72.54
GP41_I2S_2_FS11: U78.54, U79.54
GP41_I2S_2_FS12: U85.54, U86.54
GP41_I2S_2_FS13: U92.54, U93.54
GP41_I2S_2_FS14: U99.54, U100.54
GP41_I2S_2_FS15: U106.54, U107.54
GP42: U36.32, U37.32, U41.10
GP42_I2S_2_RXD: U2.50, U3.50
GP42_I2S_2_RXD1: U8.50, U9.50
GP42_I2S_2_RXD2: U15.50, U16.50
GP42_I2S_2_RXD3: U22.50, U23.50
GP42_I2S_2_RXD4: U29.50, U30.50
GP42_I2S_2_RXD5: U36.50, U37.50
GP42_I2S_2_RXD6: U43.50, U44.50
GP42_I2S_2_RXD7: U50.50, U51.50
GP42_I2S_2_RXD8: U57.50, U58.50
GP42_I2S_2_RXD9: U64.50, U65.50
GP42_I2S_2_RXD10: U71.50, U72.50
GP42_I2S_2_RXD11: U78.50, U79.50
GP42_I2S_2_RXD12: U85.50, U86.50
GP42_I2S_2_RXD13: U92.50, U93.50
GP42_I2S_2_RXD14: U99.50, U100.50
GP42_I2S_2_RXD15: U106.50, U107.50
GP43: U36.30, U37.30, U41.9
GP43_I2S_2_TXD: U2.56, U3.56
GP43_I2S_2_TXD1: U8.56, U9.56
GP43_I2S_2_TXD2: U15.56, U16.56
GP43_I2S_2_TXD3: U22.56, U23.56
GP43_I2S_2_TXD4: U29.56, U30.56
GP43_I2S_2_TXD5: U36.56, U37.56
GP43_I2S_2_TXD6: U43.56, U44.56
GP43_I2S_2_TXD7: U50.56, U51.56
GP43_I2S_2_TXD8: U57.56, U58.56
GP43_I2S_2_TXD9: U64.56, U65.56
GP43_I2S_2_TXD10: U71.56, U72.56
GP43_I2S_2_TXD11: U78.56, U79.56
GP43_I2S_2_TXD12: U85.56, U86.56
GP43_I2S_2_TXD13: U92.56, U93.56
GP43_I2S_2_TXD14: U99.56, U100.56
GP43_I2S_2_TXD15: U106.56, U107.56
GP44: U2.24, U3.24, U6.4
GP45: U2.26, U3.26, U6.7
GP46: U2.28, U3.28, U6.8
GP47: U2.30, U3.30, U6.9
GP48: U2.32, U3.32, U6.10
GP49: U2.34, U3.34
GP50: U36.28, U37.28, U41.8
GP51: U36.26, U37.26, U41.7
GP52: U36.25, U37.25
GP53: U36.24, U37.24, U41.4
GP54: U43.48, U44.48, U48.1
GP55: U43.42, U44.42
GP56: U43.34, U44.34
GP57: U43.32, U44.32, U48.10
GP58: U43.30, U44.30, U48.9
GP59: U43.28, U44.28, U48.8
GP60: U43.26, U44.26, U48.7
GP61: U43.25, U44.25
GP62: U43.24, U44.24, U48.4
GP63: U50.48, U51.48, U55.1
GP64: U50.42, U51.42
GP65: U50.34, U51.34
GP66: U50.32, U51.32, U55.10
GP67: U50.30, U51.30, U55.9
GP68: U50.28, U51.28, U55.8
GP69: U50.26, U51.26, U55.7
GP70: U50.25, U51.25
GP71: U50.24, U51.24, U55.4
GP72: U57.48, U58.48, U62.1
GP73: U57.42, U58.42
GP74: U57.34, U58.34
GP75: U57.32, U58.32, U62.10
GP76: U57.30, U58.30, U62.9
GP77: U57.28, U58.28, U62.8
GP77_SD_0_CD#: U2.60, U3.60
GP77_SD_0_CD#1: U8.60, U9.60
GP77_SD_0_CD#2: U15.60, U16.60
GP77_SD_0_CD#3: U22.60, U23.60
GP77_SD_0_CD#4: U29.60, U30.60
GP77_SD_0_CD#5: U36.60, U37.60
GP77_SD_0_CD#6: U43.60, U44.60
GP77_SD_0_CD#7: U50.60, U51.60
GP77_SD_0_CD#8: U57.60, U58.60
GP77_SD_0_CD#9: U64.60, U65.60
GP77_SD_0_CD#10: U71.60, U72.60
GP77_SD_0_CD#11: U78.60, U79.60
GP77_SD_0_CD#12: U85.60, U86.60
GP77_SD_0_CD#13: U92.60, U93.60
GP77_SD_0_CD#14: U99.60, U100.60
GP77_SD_0_CD#15: U106.60, U107.60
GP78: U57.26, U58.26, U62.7
GP78_SD_0_CLK: U2.58, U3.58
GP78_SD_0_CLK1: U8.58, U9.58
GP78_SD_0_CLK2: U15.58, U16.58
GP78_SD_0_CLK3: U22.58, U23.58
GP78_SD_0_CLK4: U29.58, U30.58
GP78_SD_0_CLK5: U36.58, U37.58
GP78_SD_0_CLK6: U43.58, U44.58
GP78_SD_0_CLK7: U50.58, U51.58
GP78_SD_0_CLK8: U57.58, U58.58
GP78_SD_0_CLK9: U64.58, U65.58
GP78_SD_0_CLK10: U71.58, U72.58
GP78_SD_0_CLK11: U78.58, U79.58
GP78_SD_0_CLK12: U85.58, U86.58
GP78_SD_0_CLK13: U92.58, U93.58
GP78_SD_0_CLK14: U99.58, U100.58
GP78_SD_0_CLK15: U106.58, U107.58
GP79: U57.25, U58.25
GP79_SD_0_CMD: U2.62, U3.62
GP79_SD_0_CMD1: U8.62, U9.62
GP79_SD_0_CMD2: U15.62, U16.62
GP79_SD_0_CMD3: U22.62, U23.62
GP79_SD_0_CMD4: U29.62, U30.62
GP79_SD_0_CMD5: U36.62, U37.62
GP79_SD_0_CMD6: U43.62, U44.62
GP79_SD_0_CMD7: U50.62, U51.62
GP79_SD_0_CMD8: U57.62, U58.62
GP79_SD_0_CMD9: U64.62, U65.62
GP79_SD_0_CMD10: U71.62, U72.62
GP79_SD_0_CMD11: U78.62, U79.62
GP79_SD_0_CMD12: U85.62, U86.62
GP79_SD_0_CMD13: U92.62, U93.62
GP79_SD_0_CMD14: U99.62, U100.62
GP79_SD_0_CMD15: U106.62, U107.62
GP80: U57.24, U58.24, U62.4
GP80_SD_0_DAT0: U2.66, U3.66
GP80_SD_0_DAT1: U8.66, U9.66
GP80_SD_0_DAT2: U15.66, U16.66
GP80_SD_0_DAT3: U22.66, U23.66
GP80_SD_0_DAT4: U29.66, U30.66
GP80_SD_0_DAT5: U36.66, U37.66
GP80_SD_0_DAT6: U43.66, U44.66
GP80_SD_0_DAT7: U50.66, U51.66
GP80_SD_0_DAT8: U57.66, U58.66
GP80_SD_0_DAT9: U64.66, U65.66
GP80_SD_0_DAT10: U71.66, U72.66
GP80_SD_0_DAT11: U78.66, U79.66
GP80_SD_0_DAT12: U85.66, U86.66
GP80_SD_0_DAT13: U92.66, U93.66
GP80_SD_0_DAT14: U99.66, U100.66
GP80_SD_0_DAT15: U106.66, U107.66
GP81: U64.48, U65.48, U69.1
GP81_SD_0_DAT1: U2.70, U3.70
GP81_SD_0_DAT2: U8.70, U9.70
GP81_SD_0_DAT3: U15.70, U16.70
GP81_SD_0_DAT4: U22.70, U23.70
GP81_SD_0_DAT5: U29.70, U30.70
GP81_SD_0_DAT6: U36.70, U37.70
GP81_SD_0_DAT7: U43.70, U44.70
GP81_SD_0_DAT8: U50.70, U51.70
GP81_SD_0_DAT9: U57.70, U58.70
GP81_SD_0_DAT10: U64.70, U65.70
GP81_SD_0_DAT11: U71.70, U72.70
GP81_SD_0_DAT12: U78.70, U79.70
GP81_SD_0_DAT13: U85.70, U86.70
GP81_SD_0_DAT14: U92.70, U93.70
GP81_SD_0_DAT15: U99.70, U100.70
GP81_SD_0_DAT16: U106.70, U107.70
GP82: U64.42, U65.42
GP82_SD_0_DAT1: U8.64, U9.64
GP82_SD_0_DAT2: U2.64, U3.64
GP82_SD_0_DAT3: U15.64, U16.64
GP82_SD_0_DAT4: U22.64, U23.64
GP82_SD_0_DAT5: U29.64, U30.64
GP82_SD_0_DAT6: U36.64, U37.64
GP82_SD_0_DAT7: U43.64, U44.64
GP82_SD_0_DAT8: U50.64, U51.64
GP82_SD_0_DAT9: U57.64, U58.64
GP82_SD_0_DAT10: U64.64, U65.64
GP82_SD_0_DAT11: U71.64, U72.64
GP82_SD_0_DAT12: U78.64, U79.64
GP82_SD_0_DAT13: U85.64, U86.64
GP82_SD_0_DAT14: U92.64, U93.64
GP82_SD_0_DAT15: U99.64, U100.64
GP82_SD_0_DAT16: U106.64, U107.64
GP83: U64.34, U65.34
GP83_SD_0_DAT1: U8.68, U9.68
GP83_SD_0_DAT2: U15.68, U16.68
GP83_SD_0_DAT3: U2.68, U3.68
GP83_SD_0_DAT4: U22.68, U23.68
GP83_SD_0_DAT5: U29.68, U30.68
GP83_SD_0_DAT6: U36.68, U37.68
GP83_SD_0_DAT7: U43.68, U44.68
GP83_SD_0_DAT8: U50.68, U51.68
GP83_SD_0_DAT9: U57.68, U58.68
GP83_SD_0_DAT10: U64.68, U65.68
GP83_SD_0_DAT11: U71.68, U72.68
GP83_SD_0_DAT12: U78.68, U79.68
GP83_SD_0_DAT13: U85.68, U86.68
GP83_SD_0_DAT14: U92.68, U93.68
GP83_SD_0_DAT15: U99.68, U100.68
GP83_SD_0_DAT16: U106.68, U107.68
GP84: U64.32, U65.32, U69.10
GP84_SD_CLK_FB: U2.44, U3.44
GP84_SD_CLK_FB1: U8.44, U9.44
GP84_SD_CLK_FB2: U15.44, U16.44
GP84_SD_CLK_FB3: U22.44, U23.44
GP84_SD_CLK_FB4: U29.44, U30.44
GP84_SD_CLK_FB5: U36.44, U37.44
GP84_SD_CLK_FB6: U43.44, U44.44
GP84_SD_CLK_FB7: U50.44, U51.44
GP84_SD_CLK_FB8: U57.44, U58.44
GP84_SD_CLK_FB9: U64.44, U65.44
GP84_SD_CLK_FB10: U71.44, U72.44
GP84_SD_CLK_FB11: U78.44, U79.44
GP84_SD_CLK_FB12: U85.44, U86.44
GP84_SD_CLK_FB13: U92.44, U93.44
GP84_SD_CLK_FB14: U99.44, U100.44
GP84_SD_CLK_FB15: U106.44, U107.44
GP85: U64.30, U65.30, U69.9
GP86: U64.28, U65.28, U69.8
GP87: U64.26, U65.26, U69.7
GP88: U64.25, U65.25
GP89: U64.24, U65.24, U69.4
GP90: U71.48, U72.48, U76.1
GP91: U71.42, U72.42
GP92: U71.34, U72.34
GP93: U71.32, U72.32, U76.10
GP94: U71.30, U72.30, U76.9
GP95: U71.28, U72.28, U76.8
GP96: U71.26, U72.26, U76.7
GP97: U71.25, U72.25
GP98: U71.24, U72.24, U76.4
GP99: U78.48, U79.48, U83.1
GP100: U78.42, U79.42
GP101: U78.34, U79.34
GP102: U78.32, U79.32, U83.10
GP103: U78.30, U79.30, U83.9
GP104: U78.28, U79.28, U83.8
GP105: U78.26, U79.26, U83.7
GP106: U78.25, U79.25
GP107: U78.24, U79.24, U83.4
GP108: U85.48, U86.48, U90.1
GP109: U85.42, U86.42
GP109_SPI_2_CLK: U2.55, U3.55, U7.3
GP109_SPI_2_CLK1: U8.55, U9.55, U14.3
GP109_SPI_2_CLK2: U15.55, U16.55, U21.3
GP109_SPI_2_CLK3: U22.55, U23.55, U28.3
GP109_SPI_2_CLK4: U29.55, U30.55, U35.3
GP109_SPI_2_CLK5: U36.55, U37.55, U42.3
GP109_SPI_2_CLK6: U43.55, U44.55, U49.3
GP109_SPI_2_CLK7: U50.55, U51.55, U56.3
GP109_SPI_2_CLK8: U57.55, U58.55, U63.3
GP109_SPI_2_CLK9: U64.55, U65.55, U70.3
GP109_SPI_2_CLK10: U71.55, U72.55, U77.3
GP109_SPI_2_CLK11: U78.55, U79.55, U84.3
GP109_SPI_2_CLK12: U85.55, U86.55, U91.3
GP109_SPI_2_CLK13: U92.55, U93.55, U98.3
GP109_SPI_2_CLK14: U99.55, U100.55, U105.3
GP109_SPI_2_CLK15: U106.55, U107.55, U112.3
GP110: U85.34, U86.34
GP110_SPI_2_FS0: U2.53, U3.53, U7.8
GP110_SPI_2_FS1: U8.53, U9.53, U14.8
GP110_SPI_2_FS2: U15.53, U16.53, U21.8
GP110_SPI_2_FS3: U22.53, U23.53, U28.8
GP110_SPI_2_FS4: U29.53, U30.53, U35.8
GP110_SPI_2_FS5: U36.53, U37.53, U42.8
GP110_SPI_2_FS6: U43.53, U44.53, U49.8
GP110_SPI_2_FS7: U50.53, U51.53, U56.8
GP110_SPI_2_FS8: U57.53, U58.53, U63.8
GP110_SPI_2_FS9: U64.53, U65.53, U70.8
GP110_SPI_2_FS10: U71.53, U72.53, U77.8
GP110_SPI_2_FS11: U78.53, U79.53, U84.8
GP110_SPI_2_FS12: U85.53, U86.53, U91.8
GP110_SPI_2_FS13: U92.53, U93.53, U98.8
GP110_SPI_2_FS14: U99.53, U100.53, U105.8
GP110_SPI_2_FS15: U106.53, U107.53, U112.8
GP111: U85.32, U86.32, U90.10
GP111_SPI_2_FS1: U2.51, U3.51, U7.9
GP111_SPI_2_FS2: U8.51, U9.51, U14.9
GP111_SPI_2_FS3: U15.51, U16.51, U21.9
GP111_SPI_2_FS4: U22.51, U23.51, U28.9
GP111_SPI_2_FS5: U29.51, U30.51, U35.9
GP111_SPI_2_FS6: U36.51, U37.51, U42.9
GP111_SPI_2_FS7: U43.51, U44.51, U49.9
GP111_SPI_2_FS8: U50.51, U51.51, U56.9
GP111_SPI_2_FS9: U57.51, U58.51, U63.9
GP111_SPI_2_FS10: U64.51, U65.51, U70.9
GP111_SPI_2_FS11: U71.51, U72.51, U77.9
GP111_SPI_2_FS12: U78.51, U79.51, U84.9
GP111_SPI_2_FS13: U85.51, U86.51, U91.9
GP111_SPI_2_FS14: U92.51, U93.51, U98.9
GP111_SPI_2_FS15: U99.51, U100.51, U105.9
GP111_SPI_2_FS16: U106.51, U107.51, U112.9
GP112: U85.30, U86.30, U90.9
GP113: U85.28, U86.28, U90.8
GP114: U85.26, U86.26, U90.7
GP114_SPI_2_RXD: U2.59, U3.59, U7.4
GP114_SPI_2_RXD1: U8.59, U9.59, U14.4
GP114_SPI_2_RXD2: U15.59, U16.59, U21.4
GP114_SPI_2_RXD3: U22.59, U23.59, U28.4
GP114_SPI_2_RXD4: U29.59, U30.59, U35.4
GP114_SPI_2_RXD5: U36.59, U37.59, U42.4
GP114_SPI_2_RXD6: U43.59, U44.59, U49.4
GP114_SPI_2_RXD7: U50.59, U51.59, U56.4
GP114_SPI_2_RXD8: U57.59, U58.59, U63.4
GP114_SPI_2_RXD9: U64.59, U65.59, U70.4
GP114_SPI_2_RXD10: U71.59, U72.59, U77.4
GP114_SPI_2_RXD11: U78.59, U79.59, U84.4
GP114_SPI_2_RXD12: U85.59, U86.59, U91.4
GP114_SPI_2_RXD13: U92.59, U93.59, U98.4
GP114_SPI_2_RXD14: U99.59, U100.59, U105.4
GP114_SPI_2_RXD15: U106.59, U107.59, U112.4
GP115: U85.25, U86.25
GP115_SPI_2_TXD: U2.57, U3.57, U7.7
GP115_SPI_2_TXD1: U8.57, U9.57, U14.7
GP115_SPI_2_TXD2: U15.57, U16.57, U21.7
GP115_SPI_2_TXD3: U22.57, U23.57, U28.7
GP115_SPI_2_TXD4: U29.57, U30.57, U35.7
GP115_SPI_2_TXD5: U36.57, U37.57, U42.7
GP115_SPI_2_TXD6: U43.57, U44.57, U49.7
GP115_SPI_2_TXD7: U50.57, U51.57, U56.7
GP115_SPI_2_TXD8: U57.57, U58.57, U63.7
GP115_SPI_2_TXD9: U64.57, U65.57, U70.7
GP115_SPI_2_TXD10: U71.57, U72.57, U77.7
GP115_SPI_2_TXD11: U78.57, U79.57, U84.7
GP115_SPI_2_TXD12: U85.57, U86.57, U91.7
GP115_SPI_2_TXD13: U92.57, U93.57, U98.7
GP115_SPI_2_TXD14: U99.57, U100.57, U105.7
GP115_SPI_2_TXD15: U106.57, U107.57, U112.7
GP116: U85.24, U86.24, U90.4
GP117: U92.48, U93.48, U97.1
GP118: U92.42, U93.42
GP119: U92.34, U93.34
GP120: U92.32, U93.32, U97.10
GP121: U92.30, U93.30, U97.9
GP122: U92.28, U93.28, U97.8
GP123: U92.26, U93.26, U97.7
GP124: U92.25, U93.25
GP125: U92.24, U93.24, U97.4
GP126: U99.48, U100.48, U104.1
GP127: U99.42, U100.42
GP128: U99.34, U100.34
GP128_UART_1_CTS: U2.65, U3.65
GP128_UART_1_CTS1: U8.65, U9.65
GP128_UART_1_CTS2: U15.65, U16.65
GP128_UART_1_CTS3: U22.65, U23.65
GP128_UART_1_CTS4: U29.65, U30.65
GP128_UART_1_CTS5: U36.65, U37.65
GP128_UART_1_CTS6: U43.65, U44.65
GP128_UART_1_CTS7: U50.65, U51.65
GP128_UART_1_CTS8: U57.65, U58.65
GP128_UART_1_CTS9: U64.65, U65.65
GP128_UART_1_CTS10: U71.65, U72.65
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
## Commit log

2014-08-11 Completed schematic.
2014-08-11 Initial component placement.
2014-08-12 More layout. Swapped 22 Ohm with 220 Ohm in schematic for power button.
2014-08-12 Added more layout to Pi connector.
2014-08-12 More layout.
2014-08-13 Finished layout for prototype.
2014-08-13 Added LED EN to silk. Enlargened section headings on schem.
2014-08-20 Updated README with a better description.
2014-09-25 Replaced Header footprint Included DCIN pin Renamed boards Renamed files Replaces power button with side shooting SMD Cleaned up dimensions
    TODO: solve power situation between VSYS and DCIN
    TODO: Add pass through via for DCIN
2014-09-26 Added Vsys-to-5V diode. Added DCIN to Vsys MOSFET. Added slants to board dimension near Pi connector for stability.
2014-10-10 Made R4 and R5 DNP. Added I2C PU solder jumper. Changed I2C PUs to 10k.
2014-10-10 Changed value from 10k to 10K to align with library
2014-10-20 Changed DC/DC output cap to 22uF. Added value to inductor.
2014-12-05 Added silk to Pi pins. Moved a few traces to straighten them or prevent bridging of pins.
2014-12-10 Added ICs to SF lib. Added pin markers to ICs. Changed routing of TXB and PCA to come straight out pins. Added mounting hole below header. Added notes to board.
2014-12-10 Corrected errors from review and QC check (see GitHub issues)
2014-12-10 Changed pin numbers in silk to GP Edison pin numbers
2014-12-10 Fixed silk on PCA. Added dimensions.
2014-12-18 Removed duplicate IC library.
2014-12-19 created v10 panels
2015-04-13 Added bug number
2015-07-30 Added table to README.
2015-07-30 Updated table in README to show * after GP on Block.
2015-07-30 Updated README with new license and version history info
2015-08-03 Added image link in README.
2015-08-03 Changed link to Pi Block page
